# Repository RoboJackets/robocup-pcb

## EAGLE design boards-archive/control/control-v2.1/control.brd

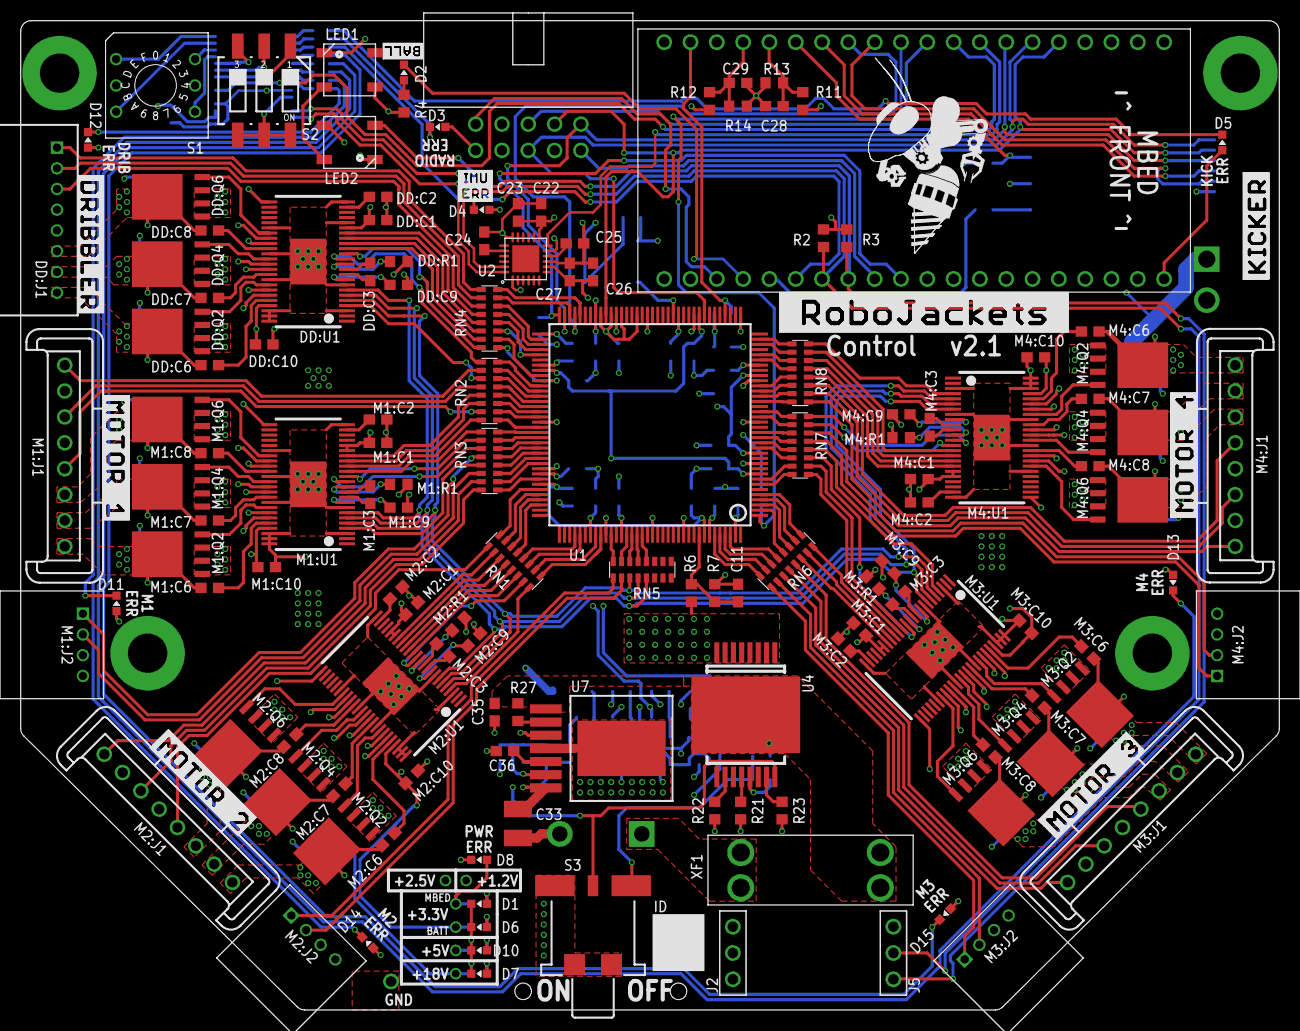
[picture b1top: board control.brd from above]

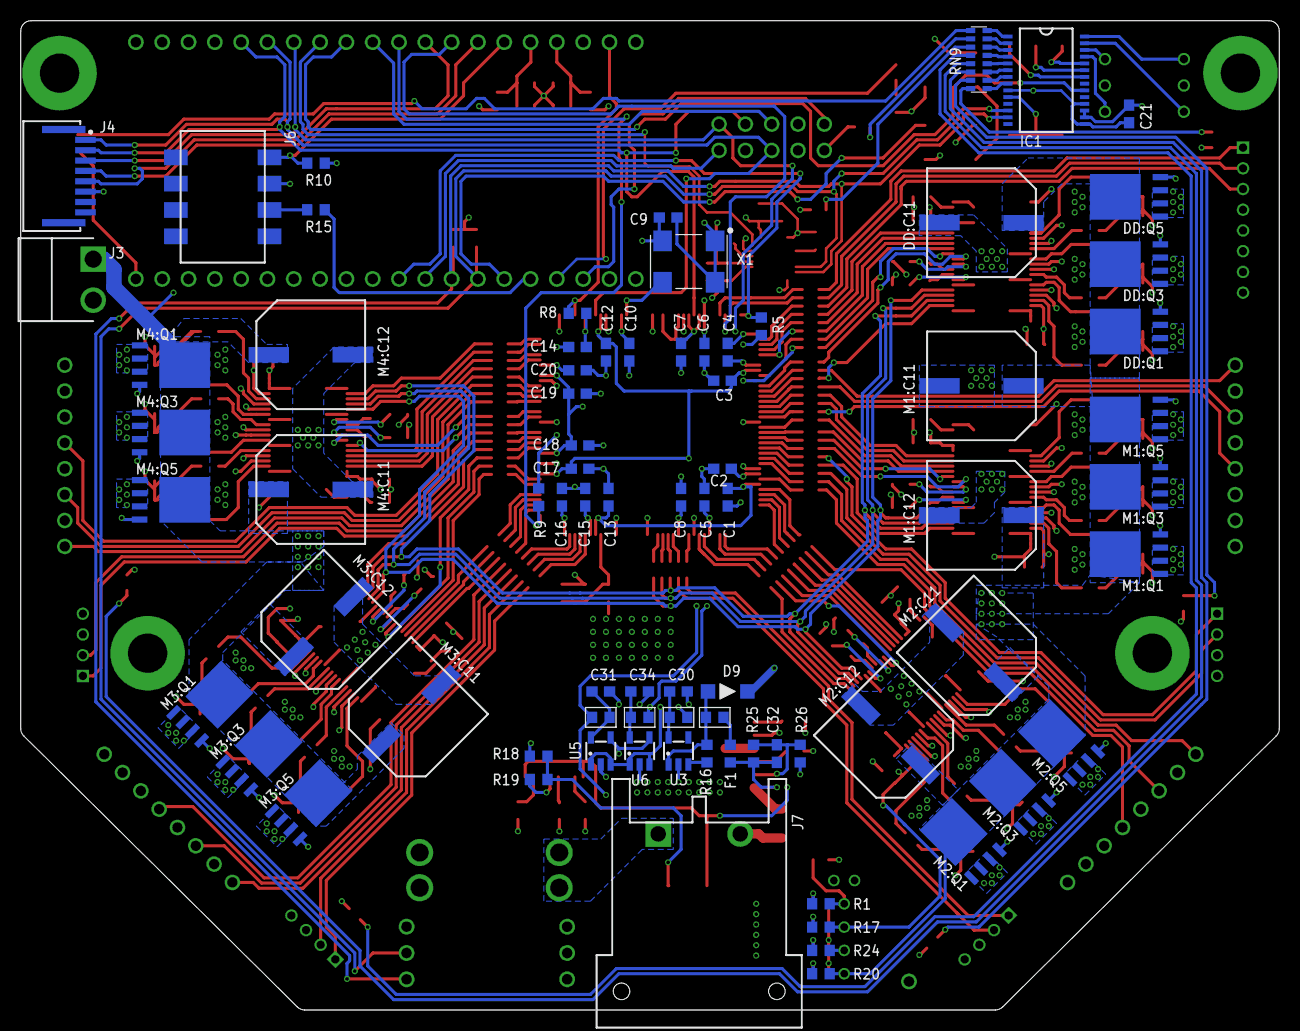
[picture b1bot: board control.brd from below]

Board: 4 copper layers, 121.5 x 95.5 mm, 223 parts (78 on the bottom side), 288 nets.

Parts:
C1, C2, C3, C4, C5, C6, C7, C8, C9, C10, C11, C12, C13, C14, C15, C16, C17, C18, C19, C20, C21, C25, C28, C29: 0.1uF; C0603
C22, C23, C27: 0.47uF; C0603
C24: 2200pF; C0603
C26: 10000pF; C0603
C30, C31, C34: 1uF; C0603
C32: 0.022uF; C0603
C33: LMK325ABJ107MM-P; C1210
C35: GRM188R6YA106MA73D; C0603
C36: 0.1uF 50V; C0603
D1, D6, D7, D10: GREEN; CHIP-LED0603
D2: BLUE; CHIP-LED0603
D3, D4, D5, D8, D11, D12, D13, D14, D15: RED; CHIP-LED0603
D9: SOD123
DD:C1, DD:C2: 1uF; C0603
DD:C3: 0.022uF 50V; C0603
DD:C6, DD:C7, DD:C8, DD:C10: 0.1uF 50V; C0603
DD:C9: 2.2uF 50V; C0603
DD:C11: UWZ1H221MCL1GS
DD:J1: 8-PIN_2MM-H; 2MM-8-H
DD:Q1, DD:Q2, DD:Q3, DD:Q4, DD:Q5, DD:Q6: IRFH7545; PQFN_5X6_E
DD:R1: 10k; R0603
DD:U1: DRV8303DCA; TSSOP-48_PAD
F1: 0603L075SLYR; F0603
IC1: MCP23017-E/SS; SSOP-28
J1: SBH11-PBPC-D05-RA; SBH11-*-D05-RA
J2, J5: 3-PIN-HEADER
J3: B2PS-VH(LF)(SN); B2PS-CENTERED
J4: HFW8R-1ST
J6: 147721-3
J7: DF22-2; DF22-2-H
KIT1: MBED_NXP_LPC1768; MBED-KIT
LED1, LED2: WS2812B; 5050
M1:C1, M1:C2, M2:C1, M2:C2, M3:C1, M3:C2, M4:C1, M4:C2: 1uF; C0603
M1:C3, M2:C3, M3:C3, M4:C3: 0.022uF 50V; C0603
M1:C6, M1:C7, M1:C8, M1:C10, M2:C6, M2:C7, M2:C8, M2:C10, M3:C6, M3:C7, M3:C8, M3:C10, M4:C6, M4:C7, M4:C8, M4:C10: 0.1uF 50V; C0603
M1:C9, M2:C9, M3:C9, M4:C9: 2.2uF 50V; C0603
M1:C11, M1:C12, M2:C11, M2:C12, M3:C11, M3:C12, M4:C11, M4:C12: UWZ1H221MCL1GS
M1:J1, M2:J1, M3:J1, M4:J1: MKS-1658
M1:J2, M2:J2, M3:J2, M4:J2: 4-PIN_2MM-H; 2MM-4-H
M1:Q1, M1:Q2, M1:Q3, M1:Q4, M1:Q5, M1:Q6, M2:Q1, M2:Q2, M2:Q3, M2:Q4, M2:Q5, M2:Q6, M3:Q1, M3:Q2, M3:Q3, M3:Q4, M3:Q5, M3:Q6, M4:Q1, M4:Q2, M4:Q3, M4:Q4, M4:Q5, M4:Q6: IRFH7545; PQFN_5X6_E
M1:R1, M2:R1, M3:R1, M4:R1: 10k; R0603
M1:U1, M2:U1, M3:U1, M4:U1: DRV8303DCA; TSSOP-48_PAD
R1, R4, R5, R15, R17: 330; R0603
R2, R3, R8, R9: 4.7k; R0603
R6, R11: 68k; R0603
R7, R10, R12, R13, R14, R16, R21: 10k; R0603
R18: 270k; R0603
R19, R27: 100k; R0603
R20, R22, R23, R24: 1k; R0603
R25: 34k; R0603
R26: 6.49k; R0603
RN1, RN2, RN3, RN4, RN5, RN6, RN7, RN8, RN9: 330; RA-8_2506
S1: 94HCB16T; HEX
S2: 219-03; CTS-219-03
S3: 34EWMSP12M6RT
SB1, SB2, SB3, SB4: SOLDERBRIDGESB0603; SB0603
U1: XC3S250E-4TQG144C; TQFP144
U2: MPU-6050; QFN-24-4MM2
U3: TLV70233DBVR; SOT-23-5
U4: VND5E006ASPTR-E; POWERSO-16
U5: MCP1824T-1202E/OT; SOT-23-5
U6: MCP1824T-2502E/OT; SOT-23-5
U7: LMZ14201; TO-PMOD-7
U$2: ROBOJACKETS
U$3: MOTOR-1
U$4: DRIBBLER
U$5: MOTOR-2
U$6: MOTOR-3
U$7: MOTOR-4
U$8: BALL
U$9: KICKER
U$10: ERR-IMU
U$11: ROBOBUZZ_1.0X2
X1: ASV-18.432MHZ-EJ-T; ASV
XF1: 30A; 3557-2

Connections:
3.3V-EN: R16.1, U3.3
3V3-LED: D6.A, R17.1
5V-LED: D10.A, R24.2
18.5V-LED: D7.A, R20.1
!CS!-FPGA: KIT1.P$13, U1.69
!CS!-KICK: J4.4, KIT1.P$14
!CS!-RADIO: J1.10, KIT1.P$29
!RST!-KICK: J4.5, KIT1.P$12
!RST!-RADIO: J1.5, KIT1.P$23
+1.2V: C3.1, C5.1, C12.1, C17.1, SB2.2, U1.9, U1.45, U1.80, U1.115
+1.2V-PRE: C31.1, SB2.1, U5.5
+2.5V: C1.1, C6.1, C13.1, C20.1, R5.2, R9.2, SB4.2, U1.30, U1.65, U1.102, U1.137
+2.5V-PRE: C34.1, SB4.1, U6.5
+3.3V: C2.1, C4.1, C7.1, C8.1, C9.1, C10.1, C14.1, C15.1, C16.1, C18.1, C19.1, C21.1, C22.1, C23.1, C26.1, C27.1, D3.A, D4.A, D5.A, D8.A, D11.A, D12.A, D13.A, D14.A, D15.A, DD:J1.5, IC1.9, IC1.15, IC1.18, J1.6, J2.2, KIT1.VOUT, LED1.1, LED2.1, R1.1, R2.2, R3.2, R4.2, R8.1, R10.2, U1.13, U1.28, U1.42, U1.49, U1.57, U1.60, U1.62, U1.64, U1.79, U1.100, U1.121, U1.138, U1.143, U2.8, U2.13, U5.1, U5.3, U6.1, U6.3, X1.1, X1.4
+3.3V-LED: D1.A, R1.2
+3V3: DD:C1.1, DD:C10.1, DD:R1.1, DD:U1.19, DD:U1.45, M1:C1.1, M1:C10.1, M1:R1.1, M1:U1.19, M1:U1.20, M1:U1.45, M2:C1.1, M2:C10.1, M2:R1.1, M2:U1.19, M2:U1.20, M2:U1.45, M3:C1.1, M3:C10.1, M3:R1.1, M3:U1.19, M3:U1.20, M3:U1.45, M4:C1.1, M4:C10.1, M4:R1.1, M4:U1.19, M4:U1.20, M4:U1.45, R17.2, SB1.2
+3V3-PRE: C30.1, SB1.1, U3.5
+5V: D9.C, KIT1.VIN, KIT1.VU, M1:J1.4, M1:J2.4, M2:J1.4, M2:J2.4, M3:J1.4, M3:J2.4, M4:J1.4, M4:J2.4, R12.1, R24.1
+5V-FUSE: C32.1, C33.1, F1.1, R25.2, U7.7
+5V-PRE: D9.A, R16.2, SB3.2, U3.1
+5V-PRE2: F1.2, SB3.1
+18.5V: DD:C11.1, DD:Q1.5678, DD:Q3.5678, DD:Q5.5678, DD:U1.25, J3.1, M1:C11.1, M1:C12.1, M1:Q1.5678, M1:Q3.5678, M1:Q5.5678, M1:U1.25, M2:C11.1, M2:C12.1, M2:Q1.5678, M2:Q3.5678, M2:Q5.5678, M2:U1.25, M3:C11.1, M3:C12.1, M3:Q1.5678, M3:Q3.5678, M3:Q5.5678, M3:U1.25, M4:C11.1, M4:C12.1, M4:Q1.5678, M4:Q3.5678, M4:Q5.5678, M4:U1.25, R6.1, R11.1, R20.2, U4.1, U4.2, U4.3, U4.4, U4.5, U4.6, U4.7, U4.8
BALL-DETECT: J6.1, KIT1.P$15, R10.1
BALL-EMIT: KIT1.P$25, R15.2
BALL-EMIT-PRE: J6.3, R15.1
BATT-FPGA: C11.1, R6.2, R7.1, U1.136
CPOUT: C24.1, U2.20
CS1: R22.2, U4.10
CS2: R23.2, U4.15
CS-DIS: R21.2, U4.12
DD-!CS: DD:U1.4, RN2.11
DD-A-H: DD:U1.13, RN2.9
DD-A-L: DD:U1.14, RN4.16
DD-B-H: DD:U1.15, RN4.15
DD-B-L: DD:U1.16, RN4.14
DD-C-H: DD:U1.17, RN4.13
DD-C-L: DD:U1.18, RN4.12
DD-H1: DD:J1.3, RN4.11
DD-H2: DD:J1.2, RN4.10
DD-H3: DD:J1.1, RN4.9
DD:AVDD: DD:C2.1, DD:U1.23
DD:BST-A: DD:C6.1, DD:U1.44
DD:BST-B: DD:C7.1, DD:U1.39
DD:BST-C: DD:C8.1, DD:U1.34
DD:CP1: DD:C3.1, DD:U1.10
DD:CP2: DD:C3.2, DD:U1.11
DD:EN-GATE: DD:R1.2, DD:U1.12
DD:GH-A: DD:Q1.4, DD:U1.43
DD:GH-B: DD:Q3.4, DD:U1.38
DD:GH-C: DD:Q5.4, DD:U1.33
DD:GL-A: DD:Q2.4, DD:U1.41
DD:GL-B: DD:Q4.4, DD:U1.36
DD:GL-C: DD:Q6.4, DD:U1.31
DD:GVDD: DD:C9.1, DD:U1.9
DD:PHASE-A: DD:C6.2, DD:J1.8, DD:Q1.1, DD:Q1.2, DD:Q1.3, DD:Q2.5678, DD:U1.42
DD:PHASE-B: DD:C7.2, DD:J1.7, DD:Q3.1, DD:Q3.2, DD:Q3.3, DD:Q4.5678, DD:U1.37
DD:PHASE-C: DD:C8.2, DD:J1.6, DD:Q5.1, DD:Q5.2, DD:Q5.3, DD:Q6.5678, DD:U1.32
DIP-1: IC1.22, S2.1
DIP-2: IC1.23, S2.2
DIP-3: IC1.24, S2.3
EN-PWR: S3.2, U4.9, U4.16, U7.3
EN-PWR-PRE: R18.1, R19.2, S3.1
FB: C32.2, R25.1, R26.2, U7.6
FPGA-CLK: U1.50, X1.3
FPGA-DONE: KIT1.P$30, R5.1, U1.72
FPGA-INIT: KIT1.P$19, R8.2, U1.40
FPGA-PROG: KIT1.P$11, R9.1, U1.1
GND: C1.2, C2.2, C3.2, C4.2, C5.2, C6.2, C7.2, C8.2, C9.2, C10.2, C11.2, C12.2, C13.2, C14.2, C15.2, C16.2, C17.2, C18.2, C19.2, C20.2, C21.2, C22.2, C23.2, C24.2, C25.2, C26.2, C27.2, C28.2, C29.2, C30.2, C31.2, C33.2, C34.2, C35.2, C36.2, D1.C, D6.C, D7.C, D10.C, DD:C1.2, DD:C2.2, DD:C9.2, DD:C10.2, DD:C11.2, DD:J1.4, DD:Q2.1, DD:Q2.2, DD:Q2.3, DD:Q4.1, DD:Q4.2, DD:Q4.3, DD:Q6.1, DD:Q6.2, DD:Q6.3, DD:U1.3, DD:U1.8, DD:U1.20, DD:U1.24, DD:U1.30, DD:U1.35, DD:U1.40, DD:U1.46, DD:U1.47, DD:U1.48, DD:U1.PAD, IC1.10, IC1.16, IC1.17, J1.7, J2.1, J3.2, J4.6, J6.2, J7.2, KIT1.GND, LED1.3, LED2.3, M1:C1.2, M1:C2.2, M1:C9.2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
GPB0: IC1.1, RN9.8
GPB1: IC1.2, RN9.7
GPB2: IC1.3, RN9.6
GPB3: IC1.4, RN9.5
GPB4: IC1.5, RN9.4
GPB5: IC1.6, RN9.3
GPB6: IC1.7, RN9.2
GPB7: IC1.8, RN9.1
HEX-0: IC1.28, S1.1
HEX-1: IC1.25, S1.2
HEX-2: IC1.27, S1.4
HEX-3: IC1.26, S1.8
INT-IO: IC1.20, KIT1.P$9
INT-MPU: KIT1.P$8, U2.12
INT-RADIO: J1.3, KIT1.P$10
LED-BALL: D2.C, KIT1.P$24
LED-BALL-PRE: D2.A, R4.1
LED-DD: D12.C, RN9.16
LED-KICK: D5.C, RN9.9
LED-M1: D11.C, RN9.15
LED-M2: D14.C, RN9.14
LED-M3: D15.C, RN9.12
LED-M4: D13.C, RN9.13
LED-MPU: D4.C, RN9.11
LED-NEO: KIT1.P$26, LED2.4
LED-RADIO: D3.C, RN9.10
M1-!CS: M1:U1.4, RN3.13
M1-A-H: M1:U1.15, RN3.9
M1-A-L: M1:U1.16, RN2.16
M1-B-H: M1:U1.13, RN3.11
M1-B-L: M1:U1.14, RN3.10
M1-C-H: M1:U1.17, RN2.14
M1-C-L: M1:U1.18, RN2.13
M1-ENC-A: M1:J2.2, RN3.14
M1-ENC-B: M1:J2.1, RN3.12
M1-H1: M1:J1.1, RN2.10
M1-H2: M1:J1.3, RN2.12
M1-H3: M1:J1.5, RN2.15
M1:AVDD: M1:C2.1, M1:U1.23
M1:BST-A: M1:C6.1, M1:U1.44
M1:BST-B: M1:C7.1, M1:U1.39
M1:BST-C: M1:C8.1, M1:U1.34
M1:CP1: M1:C3.1, M1:U1.10
M1:CP2: M1:C3.2, M1:U1.11
M1:EN-GATE: M1:R1.2, M1:U1.12
M1:GH-A: M1:Q1.4, M1:U1.43
M1:GH-B: M1:Q3.4, M1:U1.38
M1:GH-C: M1:Q5.4, M1:U1.33
M1:GL-A: M1:Q2.4, M1:U1.41
M1:GL-B: M1:Q4.4, M1:U1.36
M1:GL-C: M1:Q6.4, M1:U1.31
M1:GVDD: M1:C9.1, M1:U1.9
M1:PHASE-A: M1:C7.2, M1:J1.7, M1:Q3.1, M1:Q3.2, M1:Q3.3, M1:Q4.5678, M1:U1.37
M1:PHASE-B: M1:C6.2, M1:J1.8, M1:Q1.1, M1:Q1.2, M1:Q1.3, M1:Q2.5678, M1:U1.42
M1:PHASE-C: M1:C8.2, M1:J1.6, M1:Q5.1, M1:Q5.2, M1:Q5.3, M1:Q6.5678, M1:U1.32
M2-!CS: M2:U1.4, RN1.16
M2-A-H: M2:U1.15, RN1.13
M2-A-L: M2:U1.16, RN1.12
M2-B-H: M2:U1.13, RN1.15
M2-B-L: M2:U1.14, RN1.14
M2-C-H: M2:U1.17, RN1.11
M2-C-L: M2:U1.18, RN1.10
M2-ENC-A: M2:J2.2, RN5.10
M2-ENC-B: M2:J2.1, RN5.9
M2-H1: M2:J1.1, RN3.15
M2-H2: M2:J1.3, RN3.16
M2-H3: M2:J1.5, RN1.9
M2:AVDD: M2:C2.1, M2:U1.23
M2:BST-A: M2:C6.1, M2:U1.44
M2:BST-B: M2:C7.1, M2:U1.39
M2:BST-C: M2:C8.1, M2:U1.34
M2:CP1: M2:C3.1, M2:U1.10
M2:CP2: M2:C3.2, M2:U1.11
M2:EN-GATE: M2:R1.2, M2:U1.12
M2:GH-A: M2:Q1.4, M2:U1.43
M2:GH-B: M2:Q3.4, M2:U1.38
M2:GH-C: M2:Q5.4, M2:U1.33
M2:GL-A: M2:Q2.4, M2:U1.41
M2:GL-B: M2:Q4.4, M2:U1.36
M2:GL-C: M2:Q6.4, M2:U1.31
M2:GVDD: M2:C9.1, M2:U1.9
M2:PHASE-A: M2:C7.2, M2:J1.7, M2:Q3.1, M2:Q3.2, M2:Q3.3, M2:Q4.5678, M2:U1.37
M2:PHASE-B: M2:C6.2, M2:J1.8, M2:Q1.1, M2:Q1.2, M2:Q1.3, M2:Q2.5678, M2:U1.42
M2:PHASE-C: M2:C8.2, M2:J1.6, M2:Q5.1, M2:Q5.2, M2:Q5.3, M2:Q6.5678, M2:U1.32
M3-!CS: M3:U1.4, RN7.12
M3-A-H: M3:U1.15, RN7.9
M3-A-L: M3:U1.16, RN6.16
M3-B-H: M3:U1.13, RN7.11
M3-B-L: M3:U1.14, RN7.10
M3-C-H: M3:U1.17, RN6.15
M3-C-L: M3:U1.18, RN6.14
M3-ENC-A: M3:J2.2, RN6.10
M3-ENC-B: M3:J2.1, RN6.9
M3-H1: M3:J1.1, RN6.11
M3-H2: M3:J1.3, RN6.12
M3-H3: M3:J1.5, RN6.13
M3:AVDD: M3:C2.1, M3:U1.23
M3:BST-A: M3:C6.1, M3:U1.44
M3:BST-B: M3:C7.1, M3:U1.39
M3:BST-C: M3:C8.1, M3:U1.34
M3:CP1: M3:C3.1, M3:U1.10
M3:CP2: M3:C3.2, M3:U1.11
M3:EN-GATE: M3:R1.2, M3:U1.12
M3:GH-A: M3:Q1.4, M3:U1.43
M3:GH-B: M3:Q3.4, M3:U1.38
M3:GH-C: M3:Q5.4, M3:U1.33
M3:GL-A: M3:Q2.4, M3:U1.41
M3:GL-B: M3:Q4.4, M3:U1.36
M3:GL-C: M3:Q6.4, M3:U1.31
M3:GVDD: M3:C9.1, M3:U1.9
M3:PHASE-A: M3:C7.2, M3:J1.7, M3:Q3.1, M3:Q3.2, M3:Q3.3, M3:Q4.5678, M3:U1.37
M3:PHASE-B: M3:C6.2, M3:J1.8, M3:Q1.1, M3:Q1.2, M3:Q1.3, M3:Q2.5678, M3:U1.42
M3:PHASE-C: M3:C8.2, M3:J1.6, M3:Q5.1, M3:Q5.2, M3:Q5.3, M3:Q6.5678, M3:U1.32
M4-!CS: M4:U1.4, RN8.16
M4-A-H: M4:U1.15, RN8.15
M4-A-L: M4:U1.16, RN8.14
M4-B-H: M4:U1.13, RN7.16
M4-B-L: M4:U1.14, RN7.15
M4-C-H: M4:U1.17, RN8.13
M4-C-L: M4:U1.18, RN8.12
M4-ENC-A: M4:J2.2, RN7.14
M4-ENC-B: M4:J2.1, RN7.13
M4-H1: M4:J1.1, RN8.9
M4-H2: M4:J1.3, RN8.10
M4-H3: M4:J1.5, RN8.11
M4:AVDD: M4:C2.1, M4:U1.23
M4:BST-A: M4:C6.1, M4:U1.44
M4:BST-B: M4:C7.1, M4:U1.39
M4:BST-C: M4:C8.1, M4:U1.34
M4:CP1: M4:C3.1, M4:U1.10
M4:CP2: M4:C3.2, M4:U1.11
M4:EN-GATE: M4:R1.2, M4:U1.12
M4:GH-A: M4:Q1.4, M4:U1.43
M4:GH-B: M4:Q3.4, M4:U1.38
M4:GH-C: M4:Q5.4, M4:U1.33
M4:GL-A: M4:Q2.4, M4:U1.41
M4:GL-B: M4:Q4.4, M4:U1.36
M4:GL-C: M4:Q6.4, M4:U1.31
M4:GVDD: M4:C9.1, M4:U1.9
M4:PHASE-A: M4:C7.2, M4:J1.7, M4:Q3.1, M4:Q3.2, M4:Q3.3, M4:Q4.5678, M4:U1.37
M4:PHASE-B: M4:C6.2, M4:J1.8, M4:Q1.1, M4:Q1.2, M4:Q1.3, M4:Q2.5678, M4:U1.42
M4:PHASE-C: M4:C8.2, M4:J1.6, M4:Q5.1, M4:Q5.2, M4:Q5.3, M4:Q6.5678, M4:U1.32
MISO: J1.8, J4.1, KIT1.P$6, U1.44
MISO-AUX: DD:U1.6, M1:U1.6, M2:U1.6, M3:U1.6, M4:U1.6, RN5.12
MOSI: J1.2, J4.2, KIT1.P$5, U1.63
MOSI-AUX: DD:U1.5, M1:U1.5, M2:U1.5, M3:U1.5, M4:U1.5, RN5.11
NEO-IO: LED1.4, LED2.2
PWR-ERR: D8.C, U5.4, U6.4
R-P1: RN4.1, U1.82
R-P2: RN4.2, U1.81
R-P3: RN4.3, U1.77
R-P4: RN4.4, U1.76
R-P5: RN4.5, U1.75
R-P6: RN4.6, U1.74
R-P7: RN4.7, U1.70
R-P8: RN4.8, U1.68
R-P9: RN2.1, U1.91
R-P10: RN2.2, U1.89
R-P11: RN2.3, U1.88
R-P12: RN2.4, U1.87
R-P13: RN2.5, U1.86
R-P14: RN2.6, U1.85
R-P15: RN2.7, U1.84
R-P16: RN2.8, U1.83
R-P17: RN3.1, U1.101
R-P18: RN3.2, U1.98
R-P19: RN3.3, U1.97
R-P20: RN3.4, U1.96
R-P21: RN3.5, U1.95
R-P22: RN3.6, U1.94
R-P23: RN3.7, U1.93
R-P24: RN3.8, U1.92
R-P25: RN1.1, U1.117
R-P26: RN1.2, U1.116
R-P27: RN1.3, U1.113
R-P28: RN1.4, U1.112
R-P29: RN1.5, U1.106
R-P30: RN1.6, U1.105
R-P31: RN1.7, U1.104
R-P32: RN1.8, U1.103
R-P36: RN5.4, U1.125
R-P37: RN5.5, U1.124
R-P38: RN5.6, U1.123
R-P39: RN5.7, U1.122
R-P40: RN5.8, U1.119
R-P41: RN6.1, U1.5
R-P42: RN6.2, U1.4
R-P43: RN6.3, U1.3
R-P44: RN6.4, U1.2
R-P45: RN6.5, U1.142
R-P46: RN6.6, U1.141
R-P47: RN6.7, U1.140
R-P48: RN6.8, U1.139
R-P49: RN7.1, U1.21
R-P50: RN7.2, U1.20
R-P51: RN7.3, U1.17
R-P52: RN7.4, U1.16
R-P53: RN7.5, U1.15
R-P54: RN7.6, U1.14
R-P55: RN7.7, U1.8
R-P56: RN7.8, U1.7
R-P57: RN8.1, U1.35
R-P58: RN8.2, U1.34
R-P59: RN8.3, U1.32
R-P60: RN8.4, U1.31
R-P61: RN8.5, U1.26
R-P62: RN8.6, U1.25
R-P63: RN8.7, U1.24
R-P64: RN8.8, U1.23
REGOUT: C25.1, U2.10
RON: R27.2, U7.2
SCK: J1.1, J4.3, KIT1.P$7, U1.71
SCK-AUX: DD:U1.7, M1:U1.7, M2:U1.7, M3:U1.7, M4:U1.7, RN5.13
SCL: IC1.12, J5.2, KIT1.P$27, R2.1, U2.23
SDA: IC1.13, J5.1, KIT1.P$28, R3.1, U2.24
SENSE-BATT: C28.1, KIT1.P$16, R11.2, R13.1
SENSE-VIN: C29.1, KIT1.P$17, R12.2, R14.1
SS: C36.1, U7.5
VBATT: C35.1, R18.2, R27.1, U4.17, U7.1, XF1.3, XF1.4
VIN: J7.1, XF1.1, XF1.2

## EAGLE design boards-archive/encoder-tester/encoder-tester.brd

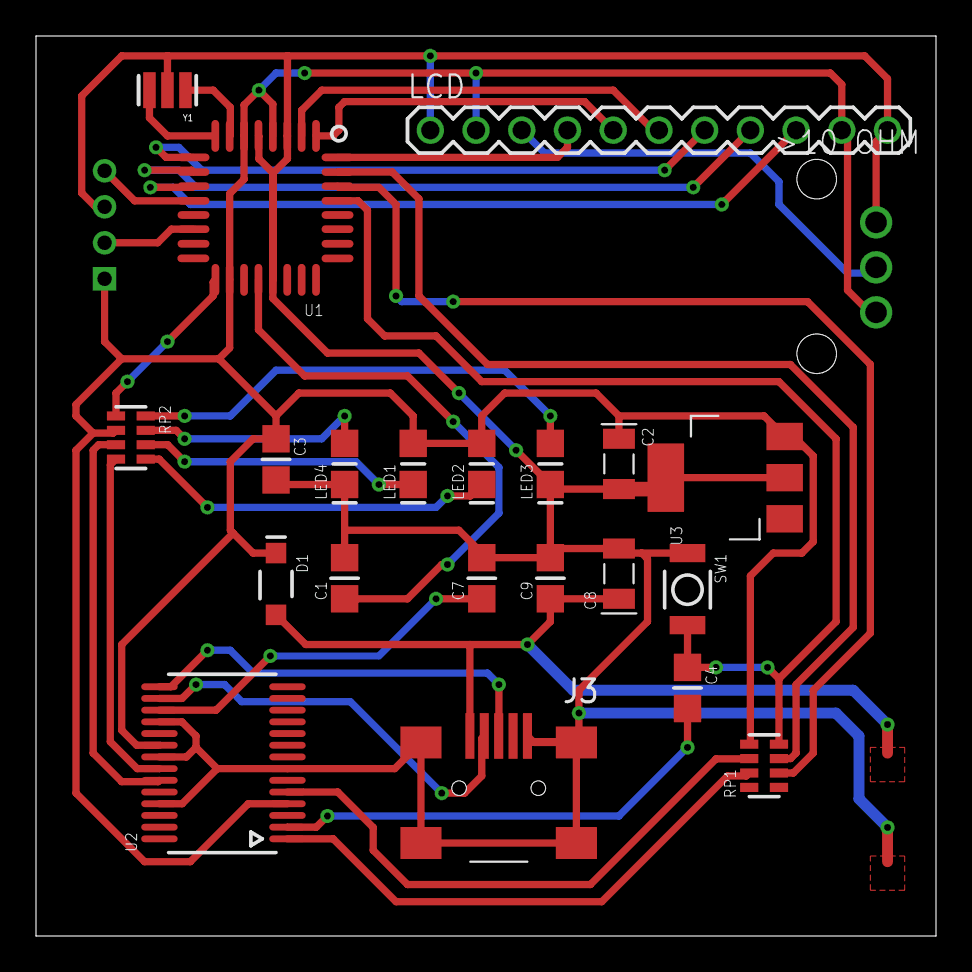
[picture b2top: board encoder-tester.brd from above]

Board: 2 copper layers, 50.0 x 50.0 mm, 23 parts (1 on the bottom side), 31 nets.

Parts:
C1, C3, C4, C7, C9: 0.1uF; CAP0805-NP
C2, C8: 4.7uF; TAN-A
D1: MBR0520; SOD-123
J3: USB-MINI-B%C; USB-MINI-B_2
J6: 2MM-4V; 2MM-4-V
LCD: M11PTH; 1X11
LED1: RED_RX; LED0805
LED2: GREEN_TX; LED0805
LED3: L_AMBER; LED0805
LED4: BLUE; LED0805
RP1: 1K; RES4NT
RP2: 330; RES4NT
SW1: RESET; 157SW
U1: ATMEGA168-20AU; QFP032
U2: FT232RL; SSOP28
U3: UA78M05; SOT223
U$7: 10OHMPOT; POTFOOT
Y1: 16MHz; RESONATOR

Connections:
3V3: C7.1, U2.17
+5V: C2.1, C3.1, D1.1, J6.1, LCD.2, LCD.10, LED1.2, LED2.2, RP1.5, RP2.2, U1.4, U1.6, U1.18, U2.4, U2.20, U3.3, U$7.1
AREF: C1.1, U1.20
COM: C1.2, C2.2, C3.2, C7.2, C8.2, C9.2, J3.1, J3.6, J3.7, J3.8, J3.9, J6.3, LCD.1, LCD.11, LED3.1, LED4.1, SW1.1, U1.3, U1.5, U1.21, U2.7, U2.18, U2.21, U2.25, U3.2, U3.4, U$7.3, Y1.2
D0/RX: RP1.2, U1.30
D1/TX: RP1.3, U1.31
D2: LCD.4, U1.32
D3: LCD.5, U1.1
D4: LCD.6, U1.2
D5: LCD.7, U1.9
D6: LCD.8, U1.10
D7: LCD.9, U1.11
D8: J6.4, U1.12
D10: J6.2, U1.14
D13/SCK: RP2.1, U1.17
unnamed: U1.8, Y1.3
unnamed: U1.7, Y1.1
unnamed: LED4.2, RP2.7
unnamed: C4.2, U2.2
unnamed: J3.3, U2.15
unnamed: J3.4, U2.16
unnamed: LED3.2, RP2.8
unnamed: RP2.3, U2.23
unnamed: RP2.4, U2.22
unnamed: LED1.1, RP2.6
unnamed: LED2.1, RP2.5
POT: LCD.3, U$7.2
RESET: C4.1, RP1.4, SW1.2, U1.29
RX: RP1.7, U2.1
TX: RP1.6, U2.5
VUSB: C8.1, C9.1, D1.2, J3.5

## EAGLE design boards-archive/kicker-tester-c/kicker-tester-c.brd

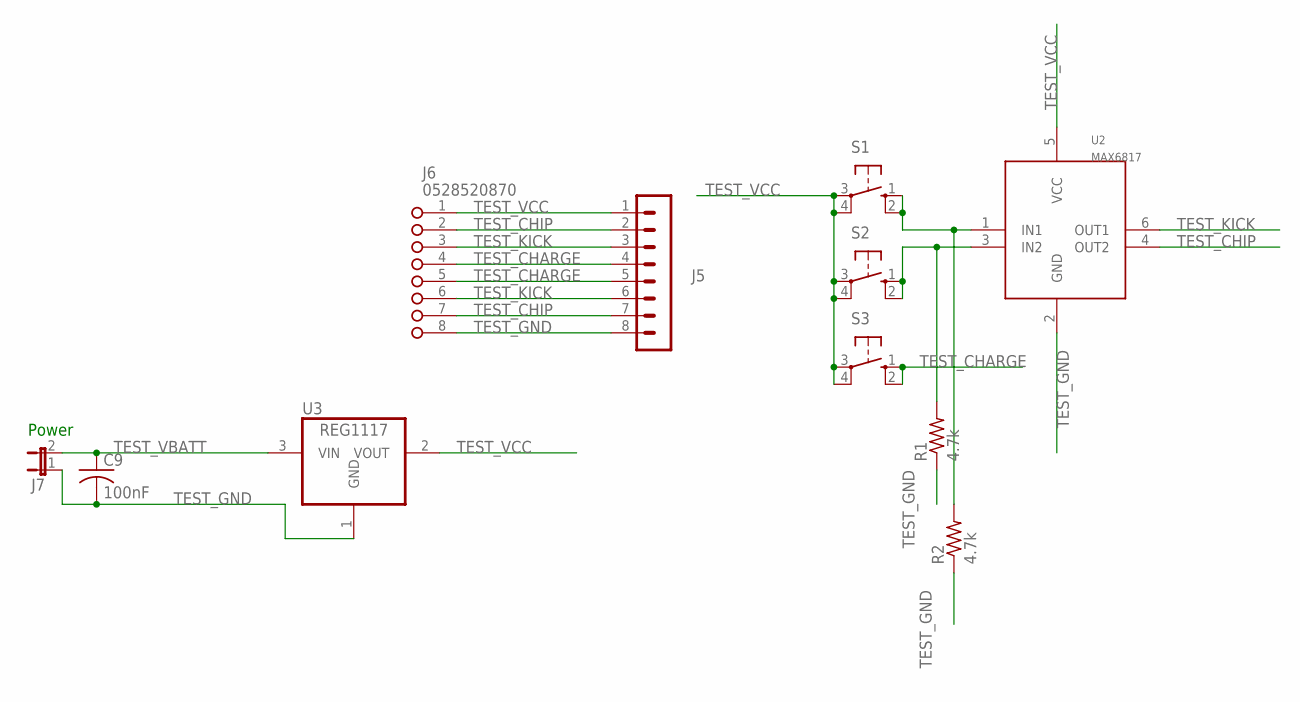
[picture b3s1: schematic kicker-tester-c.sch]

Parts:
C9: 100nF; C0603
J5: MA08-1
J6: 0528520870
J7: JP1E; JP1
R1, R2: 4.7k; 0204/7
S1, S2, S3: 10-XX; B3F-10XX
U2: MAX6817; SOT23-6
U3: REG1117; SOT223

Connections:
unnamed: R2.2, S1.1 (S), S1.2 (S1), U2.1 (IN1)
unnamed: R1.2, S2.1 (S), S2.2 (S1), U2.3 (IN2)
TEST_CHARGE: J5.4, J5.5, J6.4, J6.5, S3.1 (S), S3.2 (S1)
TEST_CHIP: J5.2, J5.7, J6.2, J6.7, U2.4 (OUT2)
TEST_GND: C9.2, J5.8, J6.8, J7.1, R1.1, R2.1, U2.2 (GND), U3.1 (GND)
TEST_KICK: J5.3, J5.6, J6.3, J6.6, U2.6 (OUT1)
TEST_VBATT: C9.1, J7.2, U3.3 (VIN)
TEST_VCC: J5.1, J6.1, S1.3, S1.4 (P1), S2.3, S2.4 (P1), S3.3, S3.4 (P1), U2.5 (VCC), U3.2 (VOUT)

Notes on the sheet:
Power

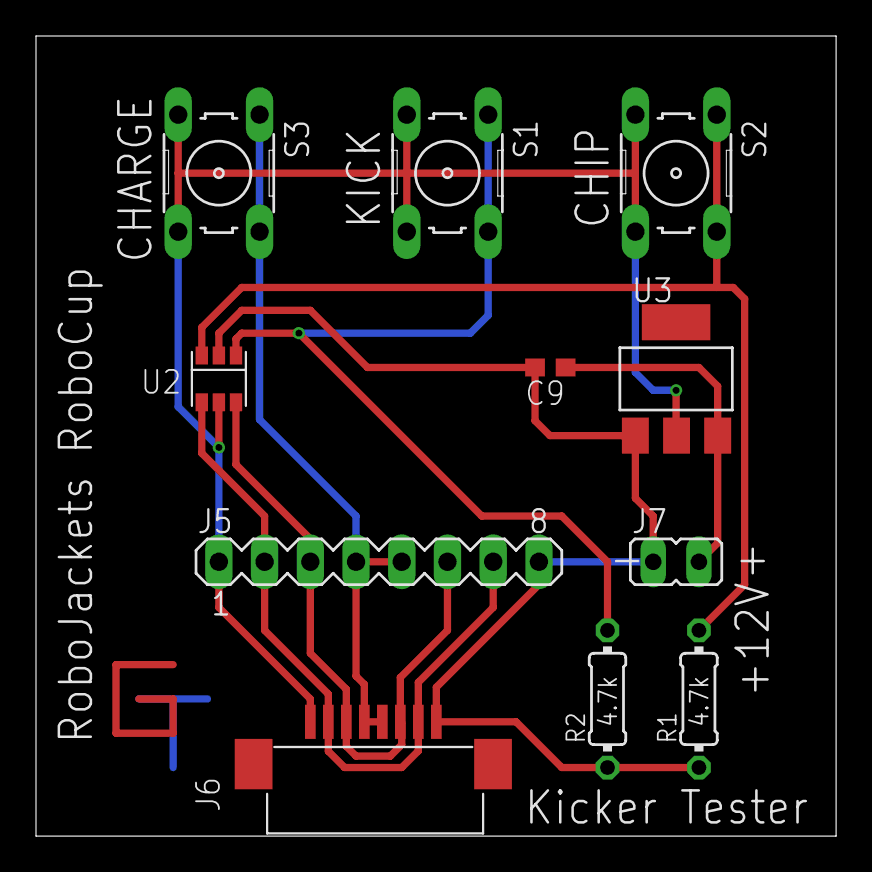
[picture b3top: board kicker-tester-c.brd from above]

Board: 2 copper layers, 44.5 x 44.5 mm, 11 parts (0 on the bottom side), 8 nets.

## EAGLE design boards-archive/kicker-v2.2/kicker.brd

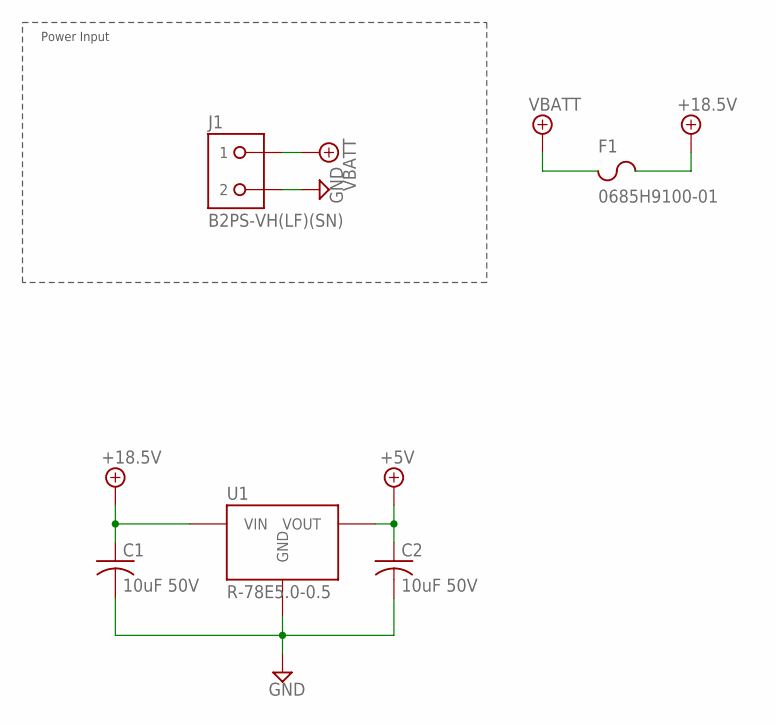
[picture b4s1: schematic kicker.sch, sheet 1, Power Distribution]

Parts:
C1, C2: 10uF 50V; C0603
F1: 0685H9100-01; F1206
J1: B2PS-VH(LF)(SN); B2PS-CENTERED
U1: R-78E5.0-0.5; R-78E

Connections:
+5V: C2.1, U1.3 (VOUT); also elsewhere on the board
+18.5V: C1.1, F1.2, U1.1 (VIN); also elsewhere on the board
GND: C1.2, C2.2, J1.2, U1.2 (GND); also elsewhere on the board
VBATT: F1.1, J1.1

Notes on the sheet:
Power Input

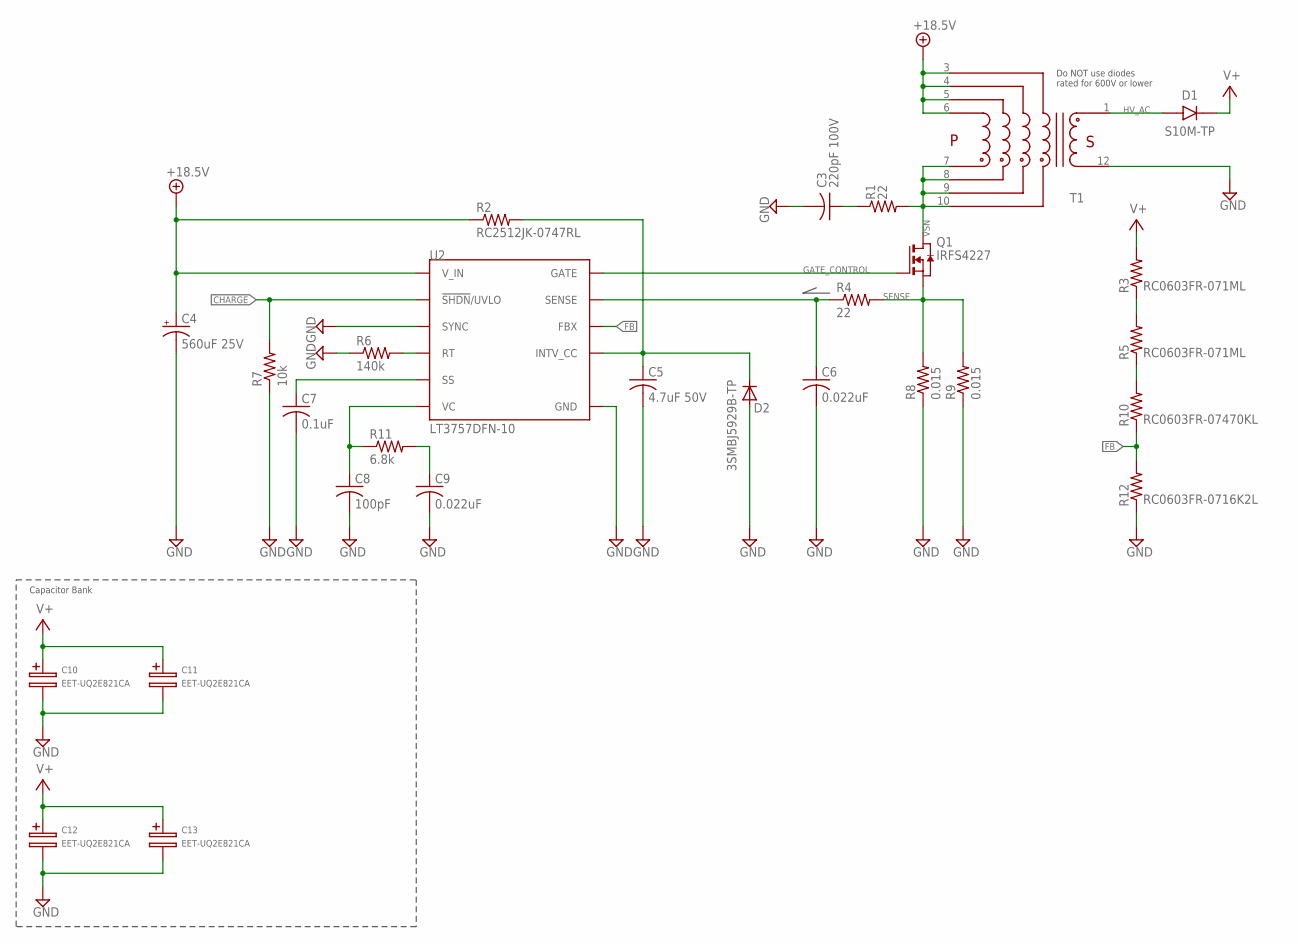
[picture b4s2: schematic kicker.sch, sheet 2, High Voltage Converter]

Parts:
C3: 220pF 100V; C0603
C4: 560uF 25V; UD-10X10_NICHICON
C5: 4.7uF 50V; C0603
C6, C9: 0.022uF; C0603
C7: 0.1uF; C0603
C8: 100pF; C0603
C10, C11: EET-UQ2E821CA; 25MM-DIA_40MM-HGT_HORIZ
C12, C13: EET-UQ2E821CA; 25MM-DIA_40MM-HGT_HORIZ_MIRRORED
D1: S10M-TP; DO-214AB
D2: 3SMBJ5929B-TP; DO214AA
Q1: IRFS4227; D2PAK
R1, R4: 22; R0805
R2: RC2512JK-0747RL; R2512
R3, R5: RC0603FR-071ML; R0603
R6: 140k; R0603
R7: 10k; R0603
R8, R9: 0.015; R1206
R10: RC0603FR-07470KL; R0603
R11: 6.8k; R0603
R12: RC0603FR-0716K2L; R0603
T1: DA203X-ALDA2034; DA2034
U2: LT3757DFN-10; DFN-10

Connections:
+18.5V: C4.+, R2.1, T1.3, T1.4, T1.5, T1.6, U2.10 (V_IN); also elsewhere on the board
CHARGE: R7.2, U2.9 (!SHDN!/UVLO); also elsewhere on the board
FB: R10.1, R12.2, U2.2 (FBX)
GATE_CONTROL: Q1.1 (G), U2.7 (GATE)
GND: C3.2, C4.-, C5.2, C6.2, C7.2, C8.2, C9.2, C10.-, C11.-, C12.-, C13.-, D2.A, R6.1, R7.1, R8.1, R9.1, R12.1, T1.12, U2.5 (SYNC), U2.PAD (GND); also elsewhere on the board
HV_AC: D1.A, T1.1
INTVCC: C5.1, D2.C, R2.2, U2.8 (INTV_CC)
unnamed: C9.1, R11.2
unnamed: C3.1, R1.1
RTIMING: R6.2, U2.4 (RT)
RTOP12: R3.1, R5.2
RTOP23: R5.1, R10.2
SENSE: Q1.3 (S), R4.2, R8.2, R9.2
SENSE_LPF: C6.1, R4.1, U2.6 (SENSE)
SOFT-START: C7.1, U2.3 (SS)
V+: C10.+, C11.+, C12.+, C13.+, D1.C, R3.2; also elsewhere on the board
VC: C8.1, R11.1, U2.1 (VC)
VSN: Q1.2 (D), R1.2, T1.7, T1.8, T1.9, T1.10

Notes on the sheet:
Do NOT use diodes rated for 600V or lower
Capacitor Bank

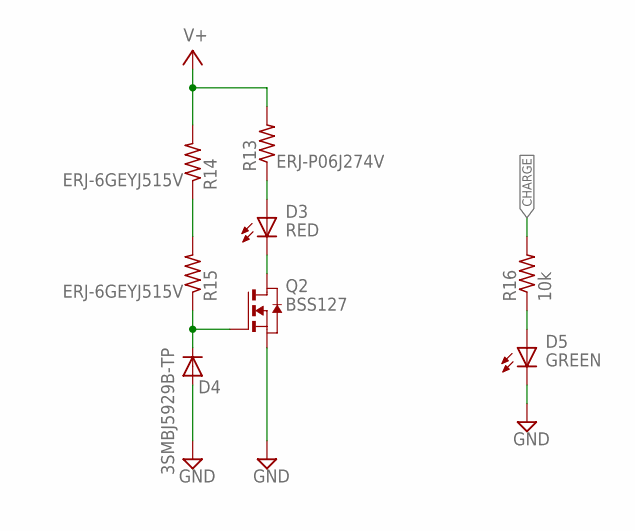
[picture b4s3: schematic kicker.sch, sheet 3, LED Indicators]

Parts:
D3: RED; CHIP-LED0603
D4: 3SMBJ5929B-TP; DO214AA
D5: GREEN; CHIP-LED0603
Q2: BSS127; SOT-23-3
R13: ERJ-P06J274V; R0805
R14, R15: ERJ-6GEYJ515V; R0805
R16: 10k; R0603

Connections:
CHARGE: R16.2; also elsewhere on the board
GND: D4.A, D5.C (K), Q2.2 (S); also elsewhere on the board
unnamed: D3.A, R13.1
unnamed: D3.C (K), Q2.3 (D)
unnamed: D5.A, R16.1
unnamed: R14.1, R15.2
unnamed: D4.C, Q2.1 (G), R15.1
V+: R13.2, R14.2; also elsewhere on the board

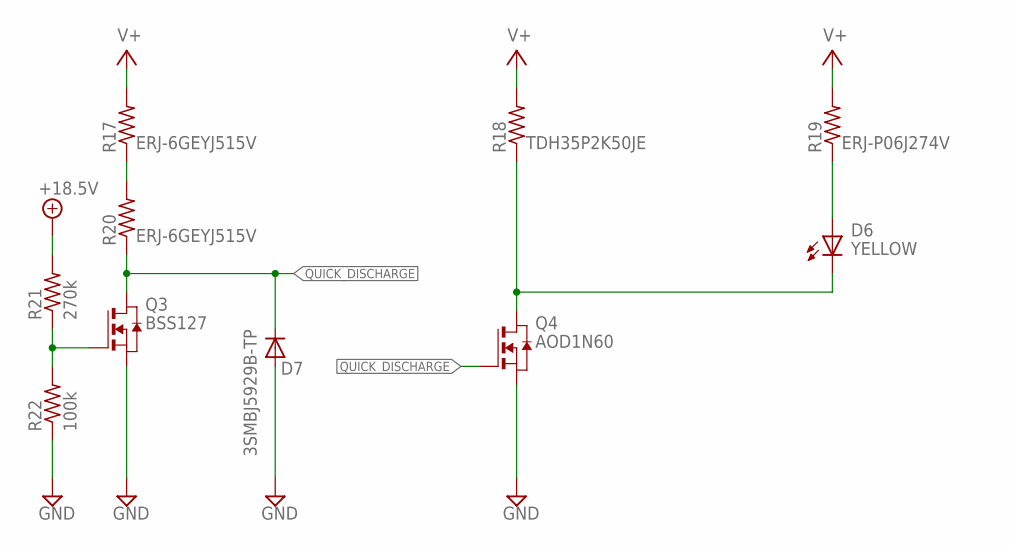
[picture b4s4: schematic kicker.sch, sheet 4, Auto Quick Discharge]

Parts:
D6: YELLOW; CHIP-LED0603
D7: 3SMBJ5929B-TP; DO214AA
Q3: BSS127; SOT-23-3
Q4: AOD1N60; DPAK
R17, R20: ERJ-6GEYJ515V; R0805
R18: TDH35P2K50JE; DPAK_TDH
R19: ERJ-P06J274V; R0805
R21: 270k; R0603
R22: 100k; R0603

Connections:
+18.5V: R21.2; also elsewhere on the board
GND: D7.A, Q3.2 (S), Q4.3 (S), R22.1; also elsewhere on the board
unnamed: R17.1, R20.2
unnamed: Q3.1 (G), R21.1, R22.2
unnamed: D6.C (K), Q4.FIN (D), R18.1 (PIN1)
unnamed: D6.A, R19.1
QUICK_DISCHARGE: D7.C, Q3.3 (D), Q4.1 (G), R20.1
V+: R17.2, R18.2 (PIN2), R19.2; also elsewhere on the board

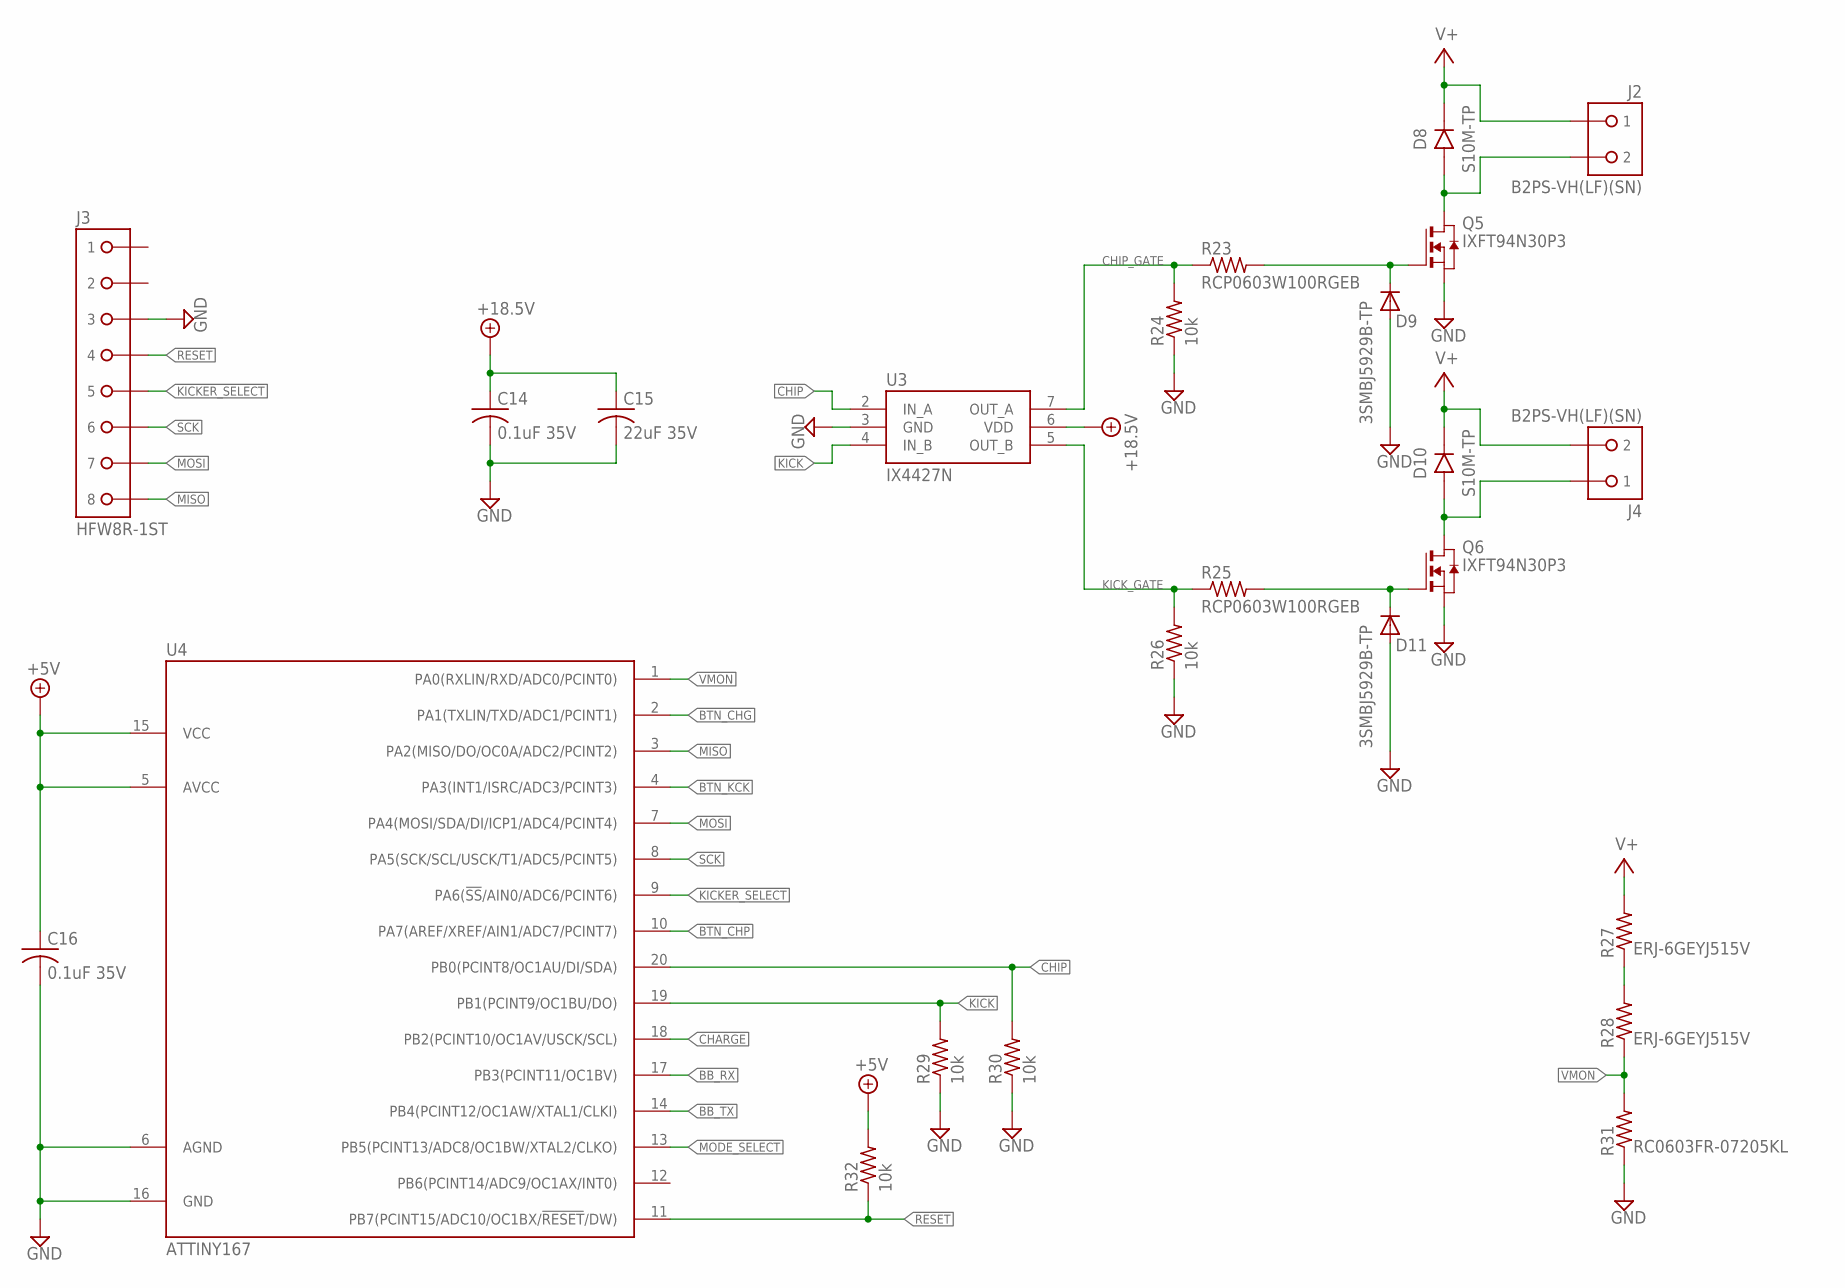
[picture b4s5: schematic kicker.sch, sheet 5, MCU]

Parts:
C14, C16: 0.1uF 35V; C0603
C15: 22uF 35V; C0805
D8, D10: S10M-TP; DO-214AB
D9, D11: 3SMBJ5929B-TP; DO214AA
J2, J4: B2PS-VH(LF)(SN); B2PS-CENTERED
J3: HFW8R-1ST
Q5, Q6: IXFT94N30P3; TO-268
R23, R25: RCP0603W100RGEB; R0603W
R24, R26, R29, R30, R32: 10k; R0603
R27, R28: ERJ-6GEYJ515V; R0805
R31: RC0603FR-07205KL; R0603
U3: IX4427N; SOIC-8
U4: ATTINY167; SOIC-20

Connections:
!BTN_CHG: U4.2 (PA1(TXLIN/TXD/ADC1/PCINT1)); also elsewhere on the board
!BTN_CHP: U4.10 (PA7(AREF/XREF/AIN1/ADC7/PCINT7)); also elsewhere on the board
!BTN_KCK: U4.4 (PA3(INT1/ISRC/ADC3/PCINT3)); also elsewhere on the board
!KICKER_SELECT: J3.5, U4.9 (PA6(!SS!/AIN0/ADC6/PCINT6))
!RESET: J3.4, R32.1, U4.11 (PB7(PCINT15/ADC10/OC1BX/!RESET!/DW))
+5V: C16.1, R32.2, U4.5 (AVCC), U4.15 (VCC); also elsewhere on the board
+18.5V: C14.1, C15.1, U3.6 (VDD); also elsewhere on the board
BB_RX: U4.17 (PB3(PCINT11/OC1BV)); also elsewhere on the board
BB_TX: U4.14 (PB4(PCINT12/OC1AW/XTAL1/CLKI)); also elsewhere on the board
CHARGE: U4.18 (PB2(PCINT10/OC1AV/USCK/SCL)); also elsewhere on the board
CHIP: R30.2, U3.2 (IN_A), U4.20 (PB0(PCINT8/OC1AU/DI/SDA))
CHIPPER: D8.A, J2.2, Q5.4 (D)
CHIP_GATE: R23.1 (PIN1), R24.2, U3.7 (OUT_A)
GND: C14.2, C15.2, C16.2, D9.A, D11.A, J3.3, Q5.3 (S), Q6.3 (S), R24.1, R26.1, R29.1, R30.1, R31.1, U3.3 (GND), U4.6 (AGND), U4.16 (GND); also elsewhere on the board
KICK: R29.2, U3.4 (IN_B), U4.19 (PB1(PCINT9/OC1BU/DO))
KICKER: D10.A, J4.1, Q6.4 (D)
KICK_GATE: R25.1 (PIN1), R26.2, U3.5 (OUT_B)
MISO: J3.8, U4.3 (PA2(MISO/DO/OC0A/ADC2/PCINT2))
MODE_SELECT: U4.13 (PB5(PCINT13/ADC8/OC1BW/XTAL2/CLKO)); also elsewhere on the board
MOSI: J3.7, U4.7 (PA4(MOSI/SDA/DI/ICP1/ADC4/PCINT4))
unnamed: D9.C, Q5.1 (G), R23.2 (PIN2)
unnamed: D11.C, Q6.1 (G), R25.2 (PIN2)
unnamed: R27.1, R28.2
SCK: J3.6, U4.8 (PA5(SCK/SCL/USCK/T1/ADC5/PCINT5))
V+: D8.C, D10.C, J2.1, J4.2, R27.2; also elsewhere on the board
VMON: R28.1, R31.2, U4.1 (PA0(RXLIN/RXD/ADC0/PCINT0))

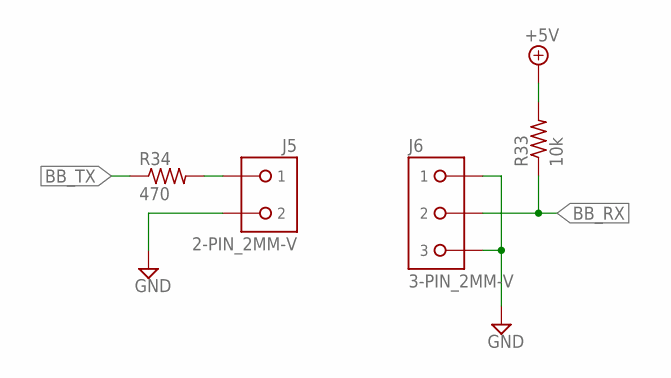
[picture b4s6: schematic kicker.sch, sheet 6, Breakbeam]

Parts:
J5: 2-PIN_2MM-V; 2MM-2-V
J6: 3-PIN_2MM-V; 2MM-3-V
R33: 10k; R0603
R34: 470; R0603

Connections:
+5V: R33.2; also elsewhere on the board
BB_RX: J6.2, R33.1; also elsewhere on the board
BB_TX: R34.1; also elsewhere on the board
GND: J5.2, J6.1, J6.3; also elsewhere on the board
unnamed: J5.1, R34.2
